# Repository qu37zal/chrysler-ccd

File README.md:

# Chrysler CCD

Reusable platform for exploring Chrysler Collision Detection (CCD) networks, decoding vehicle events, and safely experimenting with isolated module emulation. Initial reference vehicle: Elvira, a 2000 Plymouth Prowler. The archived 1997/1999 factory manual is the working design reference; electrical carryover is the working assumption, with the owner's paper 2000 factory manual available to check critical details as needed. P0 is a receive-only OBD-II sniffer; P1 is a reversible radio-interface controller. The project is designed to support research across Chrysler CCD-equipped vehicles, with vehicle-specific facts kept separate from shared protocol behavior.

## Safety status

P0's core target is a passive CCD capture from the verified Prowler DLC pair. Other DLC physical layers and full OBD-II tool behavior are stretch work. Candidate contacts from the ChryslerScanner reference include PCI/VPW (2) and SCI (6/7/9/12/14/15); these are not yet verified against the Prowler's complete DLC population. Keep the capture format extensible to separate protocol threads. P0 does not transmit. Do not connect an unvalidated prototype; never add CCD bias or termination without vehicle-specific evidence.

## Layout

- `firmware/p0-sniffer`: ESP32-S3 PlatformIO application scaffold; intended to host a local Wi-Fi AP and browser GUI.
- `lib/ccd`: transport-independent CCD frame and checksum/parser logic.
- `host`: Python capture parser, deterministic analysis/replay tools and a host-side relative autovolume controller model.
- `tests`, `fixtures`: synthetic-only protocol and analysis tests/captures.
- `docs`: requirements, safety procedures, architecture decisions, source inventory and hardware notes.
- `config/p0_threads.json`: machine-readable core CCD thread and stretch candidate DLC thread map. Candidate non-CCD contacts remain unverified for the Prowler.
- `hardware/kicad/p0_frontend`: connected 25-component CCD receiver and jumper-inhibited bench transmitter schematic; not yet a complete protected P0 board.
- `hardware/bom`: grouped DigiKey/Mouser bench purchase CSVs, with supply and completeness notes.
- `simulation`: manufacturer-model SPICE experiments, explicit measurement limits and synthetic results. LTspice is required for the current LT1716 model and successful LM5164 fixture.
- `hardware/kicad/p0_carrier`: earlier editable carrier/layout study for the ESP32-S3-DevKitC-1. It uses a generic pigtail header and has no bus receiver circuit; it is superseded by the CCD-core P0 plan in `docs/p0-bom.md` and ADR 0004. It is not a complete electrical interface or vehicle-ready PCB.
- `docs`: requirements, safety procedures, architecture decisions, source inventory and hardware notes.

## Milestones

1. **P0 core:** Obtain a genuine, timestamped, receive-only capture of Prowler CCD at the OBD-II port, with raw-frame/error/loss metadata and local Wi-Fi/USB access. The first web view can use one CCD tab.
2. **P0 stretch:** Add independently protected receiver threads for any other populated DLC protocol and a full OBD-II pass-through/sniffing mode if needed. The DLC does not expose every network or private module link in the vehicle. Active diagnostic requests and replies are later scope, not required for the first capture.
3. **Bench emulation:** isolated virtual network and reviewed module behavior, with a reusable module-emulation interface. Initial candidates are OEM radio behavior and future CCD TPMS module/sensor emulation for newer sensors; each requires protocol discovery and isolated-bench validation. No vehicle transmission without explicit owner authorization.
4. **P1:** adapter-harness controller mapping validated BCM autovolume offset changes and steering events to measured resistor-multiplexed head-unit inputs, and decoded Reverse range to a protected 12 V camera-trigger output. The model sends relative volume steps; absolute head-unit volume is neither observed nor required. P0 remains the passive capture tool used to discover these signals.

## Host tooling

Python 3.10+; run `python -m unittest discover -s tests -v`. Synthetic fixture data is explicitly labeled and is not Prowler traffic. P0 includes a local Wi-Fi access point and browser GUI; Bluetooth and a native iOS app are later possibilities and are outside initial scope.

## Firmware

Build with PlatformIO (`pio run -d firmware/p0-sniffer`). Initial target is ESP32-S3 with one CCD receive channel. USB serial and a local AP/web interface are the P0 transports. The capture record format carries a thread identifier so separately validated stretch channels can be added later. The current carrier board is superseded and must not be treated as the complete BOM or interface.

## License

License selection is pending source/license audit. Do not copy GPL implementation code into this repository until a compatible project license is chosen. Documentation and independently written code remain separately attributable.

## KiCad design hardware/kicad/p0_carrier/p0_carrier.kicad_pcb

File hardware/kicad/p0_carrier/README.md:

# P0 carrier layout study

**Status: superseded.** This artifact predates the decision to capture multiple independent DLC protocol threads. It has no J1962 board connector, power front end, or bus receiver/transmitter circuits. Do not use its PCB, DSN, SES, 3D preview, or schematic PDF as a P0 BOM or fabrication package. The current multi-thread hardware requirements and candidate BOM are in `docs/p0-bom.md`; the old board remains only as a KiCad/FreeRouting workflow example.

This KiCad project is a preliminary carrier for an ESP32-S3-DevKitC-1 and a future protected CCD receiver daughterboard. It is intentionally not a complete transceiver or vehicle-ready design.

## Layout proposal

- 88 x 38 mm two-layer carrier, subject to mechanical fit checks.
- 2x8 internal pigtail header at the J1962 end, with header pad numbers matching OBD connector pin numbers.
- Two 1x22 socket rows for the Espressif ESP32-S3-DevKitC-1 v1.1. Its USB-C connector faces the opposite end and exits through a case opening.
- 1x6 receiver mezzanine header: raw CCD candidate pair, local GND, 3V3, logic RX to DevKitC J1-4/GPIO4, and one reserved pad.
- DLC pins 3 and 11 are tentative CCD taps. The other DLC contacts remain unconnected in this layout study. Vehicle-specific pin mapping and front-end coverage are still open.
- DLC pin 16 is not connected to carrier power. This draft powers the DevKitC through USB-C; a protected 12 V input stage is future work.
- Vehicle signal ground is isolated from local logic ground by default. JP1 is an unpopulated optional link for later review after the Prowler pinout and front-end reference scheme are confirmed.

The carrier routes only the nets shown in its PCB and a small number of explicitly mapped DevKitC pins. The receiver mezzanine must provide validated input protection and threshold/hysteresis before any connection to the Prowler.

## Files and commands

`p0_carrier.kicad_sch` is a block-level engineering schematic and assumption register, not a component-level receiver circuit. `p0_carrier.kicad_pcb` is generated from `tools/build_carrier.py`. The script exports a Specctra DSN; FreeRouting routes the defined nets to a SES session; the script then imports that session back into KiCad and normalizes any router neckdowns to the 0.20 mm carrier signal width.

The current [3D fit preview](p0_carrier_3d.png) and [schematic PDF](p0_carrier_schematic.pdf) are visual aids only. The preview renders the carrier connectors, not the ESP32 DevKit itself, J1962 shell, or final enclosure.

On this workstation, KiCad CLI is `C:\Program Files\KiCad\10.0\bin\kicad-cli.exe` and FreeRouting is `%LOCALAPPDATA%\freerouting\freerouting.exe` (v2.5.0). Run from this directory:

```powershell
& 'C:\Program Files\KiCad\10.0\bin\python.exe' .\tools\build_carrier.py
& "$env:LOCALAPPDATA\freerouting\freerouting.exe" -de .\p0_carrier.dsn -do .\p0_carrier.ses --router.autorouter.max_passes=10 -mt 8
& 'C:\Program Files\KiCad\10.0\bin\python.exe' .\tools\build_carrier.py --import-ses
& 'C:\Program Files\KiCad\10.0\bin\kicad-cli.exe' pcb drc .\p0_carrier.kicad_pcb -o .\drc.txt
```

Autorouting is only a routing proposal. Review the board in KiCad and resolve the electrical, mechanical, and DRC issues before fabrication. Do not connect an unreviewed board to the vehicle.

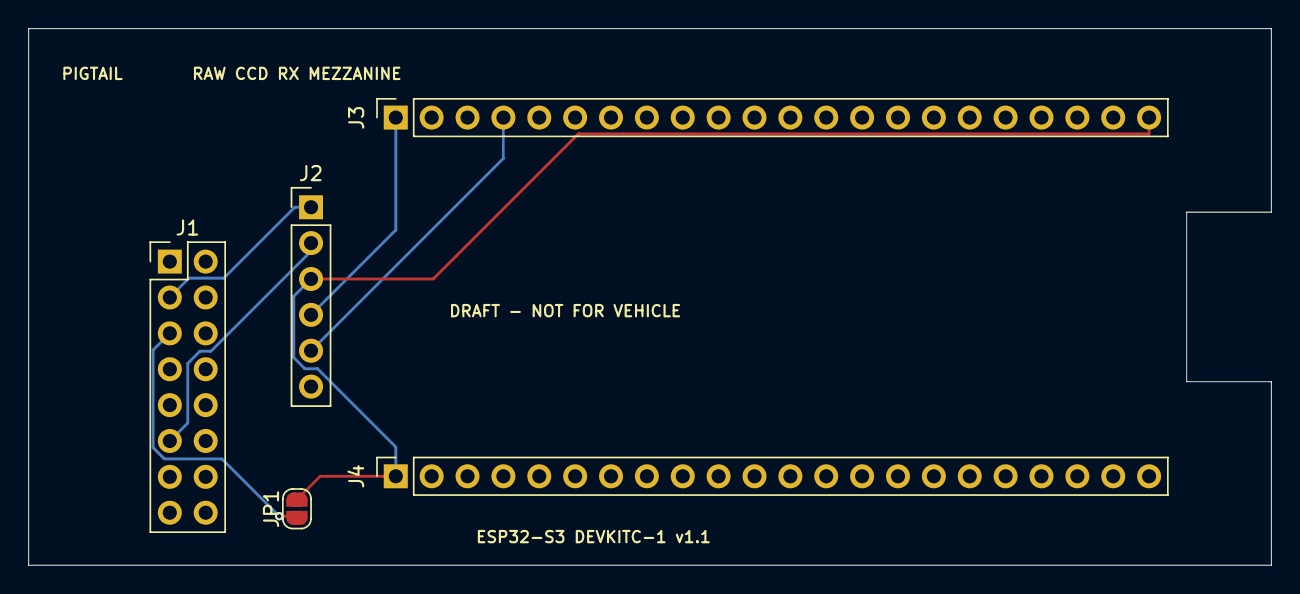
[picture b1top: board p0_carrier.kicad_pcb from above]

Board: 2 copper layers, 88.0 x 38.0 mm, 5 parts (0 on the bottom side), 6 nets.

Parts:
J1: OBD_PIGTAIL_1-16; PinHeader_2x08_P2.54mm_Vertical
J2: RX_MEZZANINE_TBD; PinHeader_1x06_P2.54mm_Vertical
J3: DEVKIT_J1; PinSocket_1x22_P2.54mm_Vertical
J4: DEVKIT_J3; PinSocket_1x22_P2.54mm_Vertical
JP1: DLC_SIG_GND_LINK_DNP; SolderJumper-2_P1.3mm_Open_RoundedPad1.0x1.5mm

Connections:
3V3: J2.4, J3.1
CCD_N_RAW: J1.11, J2.2
CCD_P_RAW: J1.3, J2.1
DLC_SIGNAL_GND: J1.5, JP1.1
LOGIC_GND: J2.3, J3.22, J4.1, JP1.2
RX_LOGIC: J2.5, J3.4
